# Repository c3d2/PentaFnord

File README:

PentaFnord README
Project Homepage: https://www.c3d2.de/wiki/index.php?title=PentaFnord

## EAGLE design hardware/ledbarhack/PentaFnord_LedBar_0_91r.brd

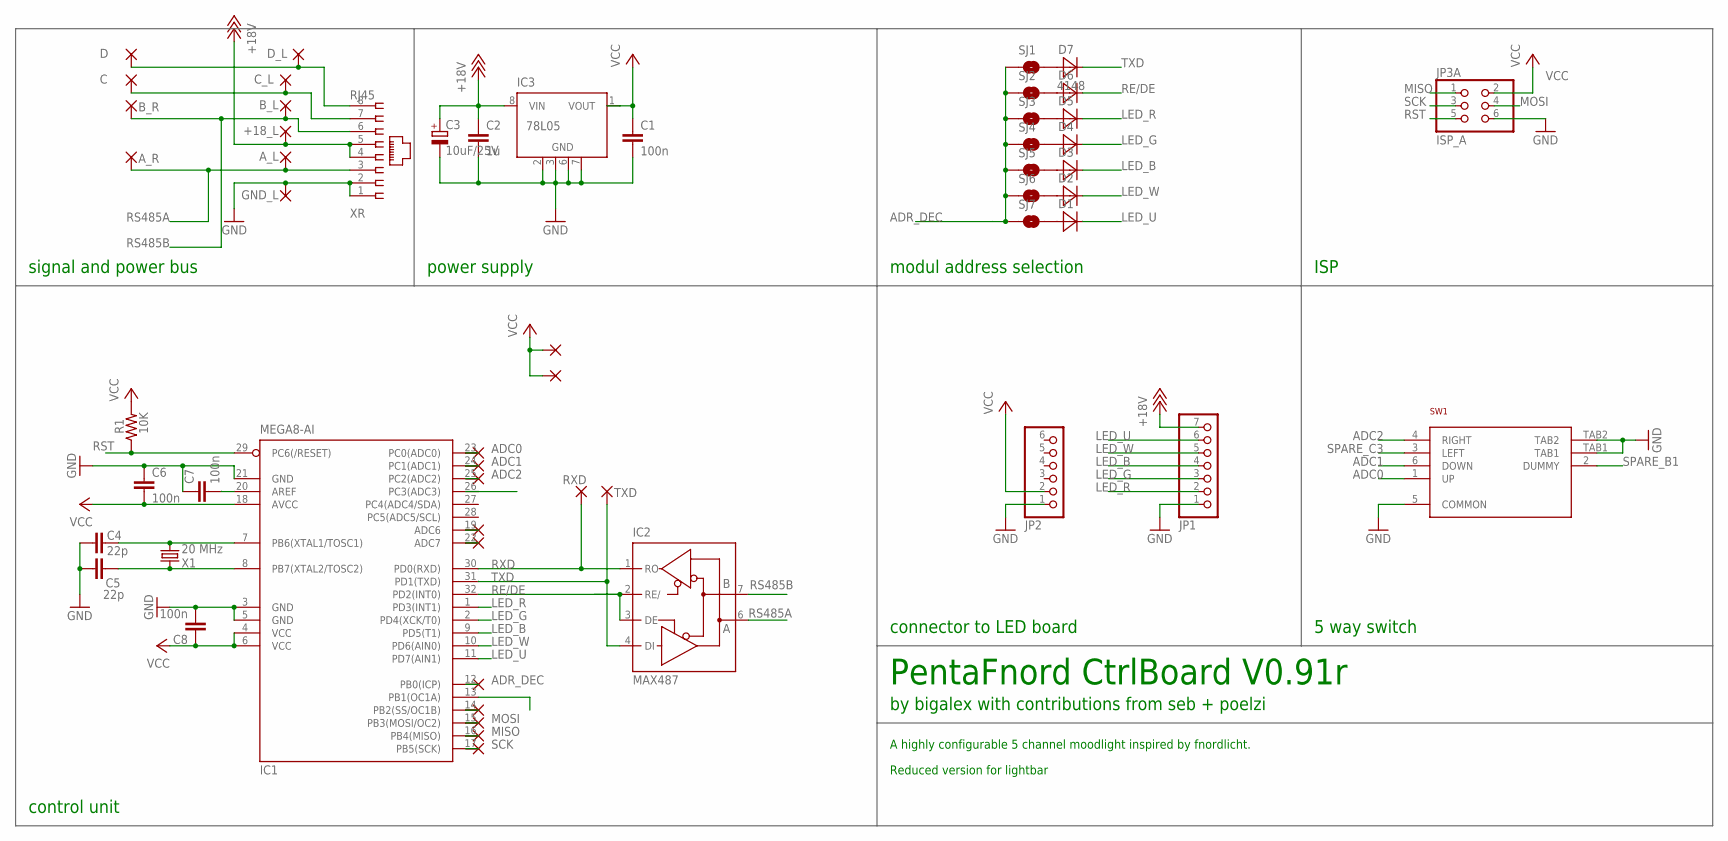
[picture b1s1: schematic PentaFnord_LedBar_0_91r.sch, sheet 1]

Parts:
+18_L: WIREPADSMD2,54-5,08; SMD2,54-5,08
ADC6, ADC7: WIREPADSMD1,27-254; SMD1,27-2,54
A_L: WIREPADSMD2,54-5,08; SMD2,54-5,08
A_R: WIREPADSMD1,27-254; SMD1,27-2,54
B_L: WIREPADSMD2,54-5,08; SMD2,54-5,08
B_R: WIREPADSMD1,27-254; SMD1,27-2,54
C: WIREPADSMD1,27-254; SMD1,27-2,54
C1, C6, C7, C8: 100n; 0805
C2: 1u; 0805
C3: 10uF/25V; SMC_D
C4, C5: 22p; 0805
C_L: WIREPADSMD2,54-5,08; SMD2,54-5,08
D: WIREPADSMD1,27-254; SMD1,27-2,54
D1, D2, D3, D4, D5, D6: DIODE_0805
D7: 4148; DIODE_0805
D_L: WIREPADSMD2,54-5,08; SMD2,54-5,08
GND_L: WIREPADSMD2,54-5,08; SMD2,54-5,08
IC1: MEGA8-AI; TQFP32-08
IC2: MAX487; SO08
IC3: 78L05; SO08
JP1: PINHD-1X07_2.54-SMD-REVERSE; 1X07SMD-REVERSE
JP2: PINHD-1X06_2.54-SMD; 1X06SMD
JP3A: ISP_A; 2X03SMD
PAD3, PAD4: WIREPADSMD1,27-254; SMD1,27-2,54
PB0, PB2, PB3, PB4, PB5: WIREPADSMD1,27-254; SMD1,27-2,54
PC0, PC1, PC2: WIREPADSMD1,27-254; SMD1,27-2,54
R1: 10K; 0805
RXD: WIREPADSMD2,54-5,08; SMD2,54-5,08
SJ1, SJ2, SJ3, SJ4, SJ5, SJ6, SJ7: SOLDERJUMPERNO; SJ_2S-NO
SW1: MCMT5-F-VADAPTED_FOOTPRINT; MCMT5-F-V_ADAPTED
TXD: WIREPADSMD2,54-5,08; SMD2,54-5,08
X1: 20 MHz; HC49UP-SMALL
XR: RJ45; 85502-5008-SMALL

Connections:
+18V: +18_L.1, C2.1, C3.+, IC3.8 (VIN), JP1.7, XR.4, XR.5
ADC0: IC1.23 (PC0(ADC0)), PC0.1, SW1.1 (UP)
ADC1: IC1.24 (PC1(ADC1)), PC1.1, SW1.6 (DOWN)
ADC2: IC1.25 (PC2(ADC2)), PC2.1, SW1.4 (RIGHT)
ADR_DEC: IC1.12 (PB0(ICP)), PB0.1, SJ1.1, SJ2.1, SJ3.1, SJ4.1, SJ5.1, SJ6.1, SJ7.1
GND: C1.2, C2.2, C3.-, C4.1, C5.1, C6.1, C7.1, C8.2, GND_L.1, IC1.3 (GND), IC1.5 (GND), IC1.21 (GND), IC2.5 (GND), IC3.2 (GND), IC3.3 (GND), IC3.6 (GND), IC3.7 (GND), JP1.1, JP2.1, JP3A.6, SW1.5 (COMMON), SW1.TAB1, SW1.TAB2, XR.1, XR.2
LED_B: D3.1 (C), IC1.9 (PD5(T1)), JP1.4
LED_G: D4.1 (C), IC1.2 (PD4(XCK/T0)), JP1.3
LED_R: D5.1 (C), IC1.1 (PD3(INT1)), JP1.2
LED_U: D1.1 (C), IC1.11 (PD7(AIN1)), JP1.6
LED_W: D2.1 (C), IC1.10 (PD6(AIN0)), JP1.5
MISO: IC1.16 (PB4(MISO)), JP3A.1, PB4.1
MOSI: IC1.15 (PB3(MOSI/OC2)), JP3A.4, PB3.1
unnamed: C.1, C_L.1, XR.7
unnamed: D.1, D_L.1, XR.8
unnamed: ADC6.1, IC1.19 (ADC6)
unnamed: ADC7.1, IC1.22 (ADC7)
unnamed: C5.2, IC1.8 (PB7(XTAL2/TOSC2)), X1.2
unnamed: C4.2, IC1.7 (PB6(XTAL1/TOSC1)), X1.1
unnamed: C7.2, IC1.20 (AREF)
unnamed: D7.2 (A), SJ1.2
unnamed: D6.2 (A), SJ2.2
unnamed: D5.2 (A), SJ3.2
unnamed: D4.2 (A), SJ4.2
unnamed: D3.2 (A), SJ5.2
unnamed: D2.2 (A), SJ6.2
unnamed: D1.2 (A), SJ7.2
unnamed: IC1.14 (PB2(SS/OC1B)), PB2.1
RE/DE: D6.1 (C), IC1.32 (PD2(INT0)), IC2.2 (RE/), IC2.3 (DE)
RS485A: A_L.1, A_R.1, IC2.6 (A), XR.3
RS485B: B_L.1, B_R.1, IC2.7 (B), XR.6
RST: IC1.29 (PC6(/RESET)), JP3A.5, R1.1
RXD: IC1.30 (PD0(RXD)), IC2.1 (RO), RXD.1
SCK: IC1.17 (PB5(SCK)), JP3A.3, PB5.1
SPARE_B1: IC1.13 (PB1(OC1A)), SW1.2 (DUMMY)
SPARE_C3: IC1.26 (PC3(ADC3)), SW1.3 (LEFT)
TXD: D7.1 (C), IC1.31 (PD1(TXD)), IC2.4 (DI), TXD.1
VCC: C1.1, C6.2, C8.1, IC1.4 (VCC), IC1.6 (VCC), IC1.18 (AVCC), IC2.8 (VCC), IC3.1 (VOUT), JP2.2, JP3A.2, PAD3.1, PAD4.1, R1.2

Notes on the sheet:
signal and power bus
power supply
control unit
PentaFnord CtrlBoard V0.91r
by bigalex with contributions from seb + poelzi
A highly configurable 5 channel moodlight inspired by fnordlicht.
modul address selection
ISP
connector to LED board
5 way switch
Reduced version for lightbar

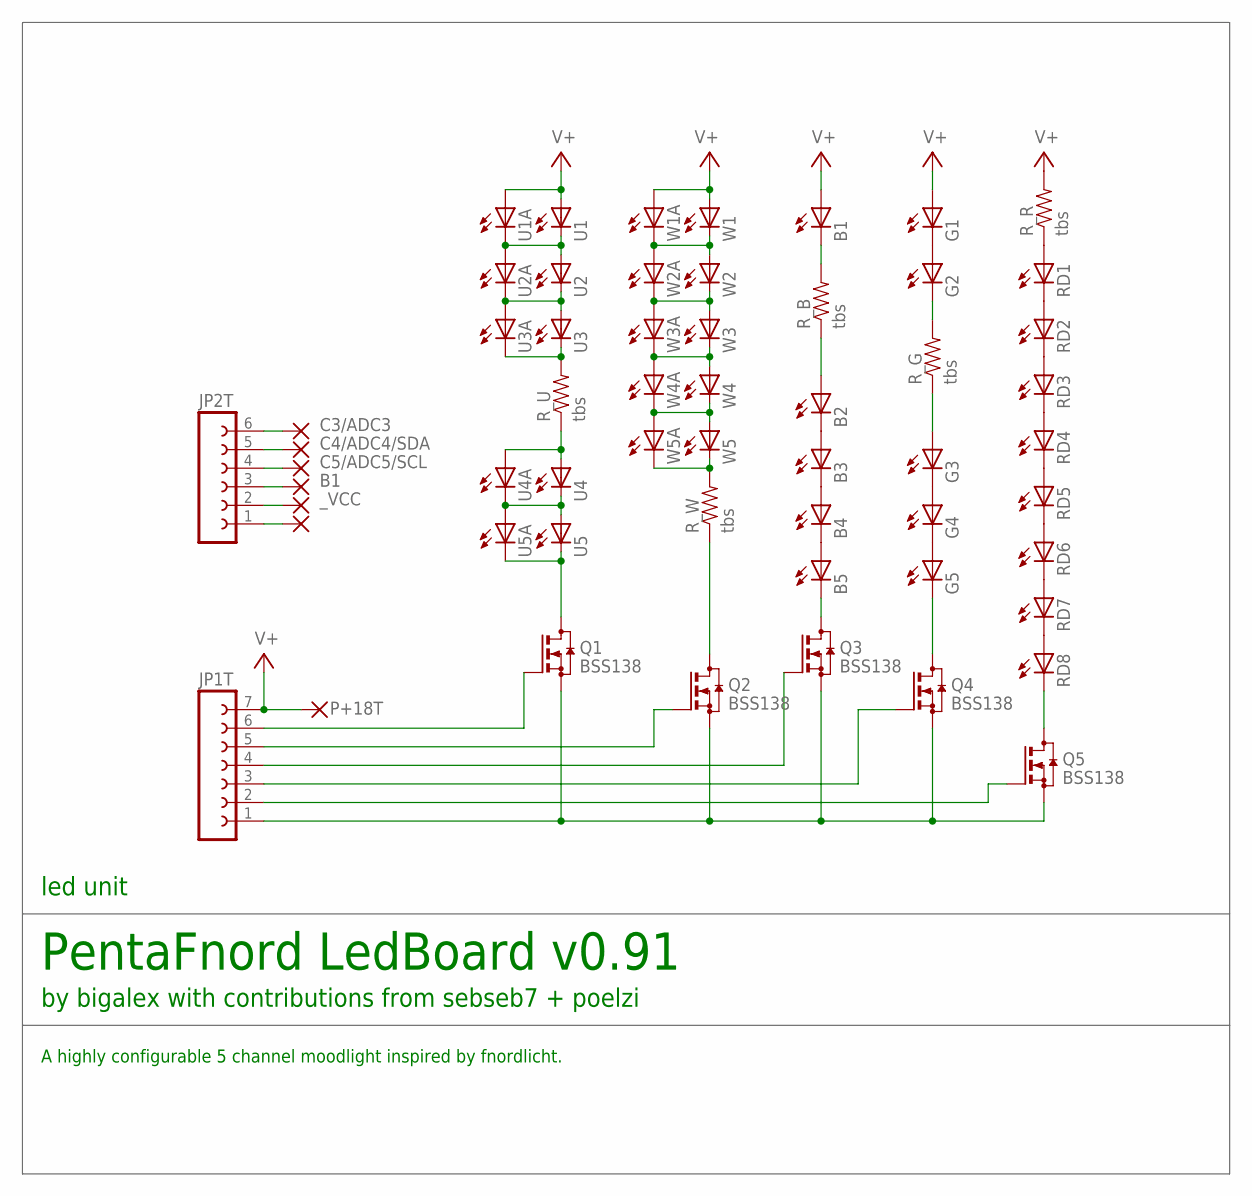
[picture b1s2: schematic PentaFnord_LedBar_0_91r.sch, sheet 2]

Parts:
B1, B2, B3, B4, B5: LED5MM
G1, G2, G3, G4, G5: LED5MM
JP1T: FE07-1; FE07
JP2T: FE06-1; FE06
P+5T, P+18T: WIREPAD2,54/0,8; 2,54/0,8
PB1T: WIREPAD2,54/0,8; 2,54/0,8
PC3T, PC4T, PC5T: WIREPAD2,54/0,8; 2,54/0,8
PGNDT1: WIREPAD2,54/0,8; 2,54/0,8
Q1, Q2, Q3, Q4, Q5: BSS138; SOT23
RD1, RD2, RD3, RD4, RD5, RD6, RD7, RD8: LED5MM
R_B: tbs; 1206
R_G: tbs; 1206
R_R: tbs; 1206
R_U: tbs; 1206
R_W: tbs; 1206
U1, U2, U3, U4, U5: NICHIA_NSSL157T-H3; PLCC2
U1A, U2A, U3A, U4A, U5A: LED5MM
W1, W2, W3, W4, W5: NICHIA_NSSL157T-H3
W1A, W2A, W3A, W4A, W5A: LED5MM

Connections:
B1: JP2T.3, PB1T.1
C3/ADC3: JP2T.6, PC3T.1
C4/ADC4/SDA: JP2T.5, PC4T.1
C5/ADC5/SCL: JP2T.4, PC5T.1
GND_T: JP1T.1, JP2T.1, PGNDT1.1, Q1.2 (S), Q2.2 (S), Q3.2 (S), Q4.2 (S), Q5.2 (S)
unnamed: U1.P$1 (C), U1A.K (C), U2.P$2 (A), U2A.A
unnamed: W4.K@1 (C), W4A.K (C), W5.A@2 (A), W5A.A
unnamed: Q1.3 (D), U5.P$1 (C), U5A.K (C)
unnamed: Q2.3 (D), R_W.1
unnamed: W3.K@1 (C), W3A.K (C), W4.A@2 (A), W4A.A
unnamed: R_U.2, U3.P$1 (C), U3A.K (C)
unnamed: U2.P$1 (C), U2A.K (C), U3.P$2 (A), U3A.A
unnamed: U4.P$1 (C), U4A.K (C), U5.P$2 (A), U5A.A
unnamed: G1.K (C), G2.A
unnamed: B5.K (C), Q3.3 (D)
unnamed: G3.K (C), G4.A
unnamed: G4.K (C), G5.A
unnamed: B2.K (C), B3.A
unnamed: B3.K (C), B4.A
unnamed: B4.K (C), B5.A
unnamed: G5.K (C), Q4.3 (D)
unnamed: RD1.K (C), RD2.A
unnamed: RD2.K (C), RD3.A
unnamed: RD3.K (C), RD4.A
unnamed: RD4.K (C), RD5.A
unnamed: RD5.K (C), RD6.A
unnamed: RD6.K (C), RD7.A
unnamed: RD1.A, R_R.1
unnamed: RD7.K (C), RD8.A
unnamed: B1.K (C), R_B.2
unnamed: Q5.3 (D), RD8.K (C)
unnamed: B2.A, R_B.1
unnamed: G2.K (C), R_G.2
unnamed: G3.A, R_G.1
unnamed: W2.K@1 (C), W2A.K (C), W3.A@2 (A), W3A.A
unnamed: R_U.1, U4.P$2 (A), U4A.A
unnamed: R_W.2, W5.K@1 (C), W5A.K (C)
unnamed: JP1T.6, Q1.1 (G)
unnamed: JP1T.5, Q2.1 (G)
unnamed: JP1T.3, Q4.1 (G)
unnamed: JP1T.4, Q3.1 (G)
unnamed: JP1T.2, Q5.1 (G)
unnamed: W1.K@1 (C), W1A.K (C), W2.A@2 (A), W2A.A
V+: B1.A, G1.A, JP1T.7, P+18T.1, R_R.2, U1.P$2 (A), U1A.A, W1.A@2 (A), W1A.A
_VCC: JP2T.2, P+5T.1

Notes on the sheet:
led unit
PentaFnord LedBoard v0.91
by bigalex with contributions from sebseb7 + poelzi
A highly configurable 5 channel moodlight inspired by fnordlicht.

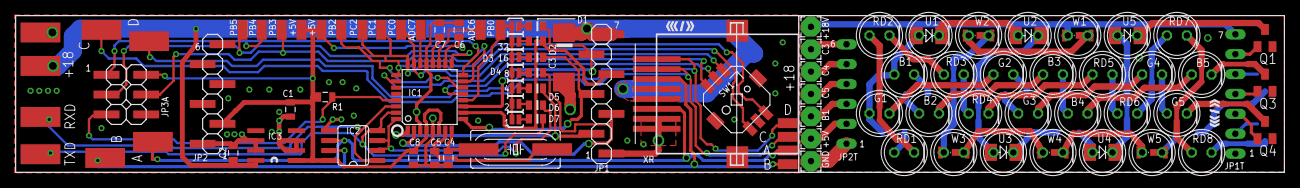
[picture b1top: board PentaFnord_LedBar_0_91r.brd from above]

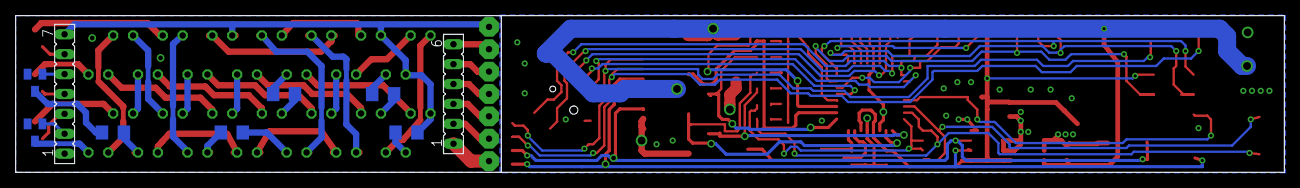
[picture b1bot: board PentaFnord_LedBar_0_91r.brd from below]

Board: 2 copper layers, 162.0 x 20.0 mm, 113 parts (9 on the bottom side), 83 nets.

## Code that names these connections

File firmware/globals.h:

/*
 * PentaFnord Firmware
 *
 * by Alexander Lorz <bigalex@gmx.de>
 *
 *
 * Parts of this software are derived work, originating from the fine
 * fnordlicht firmware (see http://lochraster.org/fnordlichtmini)
 * by Alexander Neumann <alexander@bumpern.de> and Lars Noschinski
 * <lars@public.noschinski.de>, originally published and of course
 * republished under the terms of the GNU General Public License version 3
 *
 * This program is free software: you can redistribute it and/or modify it
 * under the terms of the GNU General Public License version 3 as published by
 * the Free Software Foundation.
 *
 * This program is distributed in the hope that it will be useful, but WITHOUT
 * ANY WARRANTY; without even the implied warranty of MERCHANTABILITY or
 * FITNESS FOR A PARTICULAR PURPOSE.  See the GNU General Public License for
 * more details.
 *
 * You should have received a copy of the GNU General Public License along with
 * this program.  If not, see <http://www.gnu.org/licenses/>.
 */

#ifndef GLOBALS_H
#define GLOBALS_H

//#include <stdbool.h>
#include <avr/version.h>
#include "lib/common.h"


/* check for avr-libc version */
#if __AVR_LIBC_VERSION__ < 10600UL
#error "newer libc version (>= 1.6.0) needed!"
#endif

/* check if cpu speed is defined */
#ifndef F_CPU
#error "please define F_CPU! (see Makefile)"
#endif

/* check if this cpu is supported */
#if !(defined(__AVR_ATmega48__) || defined(__AVR_ATmega168__))
#error "this cpu is not supported yet!"
#endif

/* Port D is used for PWM with:
 * 		PD3: red
 * 		PD4: green
 * 		PD5: blue
 * 		PD6: white
 * 		PD7: ultra violet
 */

#define PWM_PORT D
#define PWM_CHANNELS 5
#define PWM_SHIFT 3
#define PWM_CHANNEL_MASK (_BV(PD3) | _BV(PD4) | _BV(PD5) | _BV(PD6)| _BV(PD7))	//This is Red Green Blue White UV

/* min brightness level */
#define PWM_MIN_BRIGHTNESS 0

#ifndef EXTERN
#define EXTERN extern
#endif


EXTERN uint8_t G_hwaddr;
EXTERN uint8_t G_swaddr;



#endif				/* GLOBALS_H */

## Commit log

2011-09-24 initial version of README
2011-09-25 Initial Version of schematics and board layout
2011-10-03 Not entirely incomplete version of schematics. LED placement on PCB allowing for 25mm x 25 mm profile (assembled PCB width < 21 mm)
2011-10-04 Routed I2C to upper board. Pullup resistors for I2C added.
2011-10-05 Board interconector placement, RJ45 SMD footprint added, modul address decoding added, lots of other improvements
2011-10-06 Upper board routed
2011-10-07 Started Layout of bottom PCB
2011-10-07 some routing done, but more left
2011-10-08 Some routing improvements, replaced 1805 by smaller 78L05
2011-10-09 Some more routing done
2011-10-10 Even much more routing done
2011-10-11 routing
2011-10-11 some ripup due to insufficient groundpath in groundplane
2011-10-12 some routing
2011-10-13 routin
2011-10-19 routing, placement print, bigger blocking Cs, value for basis resistor adapted
2011-10-19 labeling
2011-10-20 groundplanes, placement print placing, some renaming of components
2011-10-21 parts enumeration, placement print
2011-10-21 nearing completion. all labels for names and placement ... ummm ... placed
2011-10-22 Teileliste erstellt
2011-10-22 Renaming for save experimenting with 5-way-switch instead of 3 tactile buttons
2011-10-22 Initial checkin. Trying to integrate a 5-way-switch.
2011-10-23 Some schematics beautification. 5 way switch fully integrated
2011-10-23 Replacded 1206 resistors for RGBU-Leds with 805 to avoid keepout problems. Version imprint on boards updated.
2011-10-23 partslist updated
2011-10-23 Pinout-Doku added
2011-10-28 version 3 created for integrating feedback
2011-11-01 Integrating recoomendations and improvements
2011-11-17 Added optional terminator an bias resistors for RS485 (with solder jumpers)
2011-11-21 polishing routing
2011-11-24 moar features, will hack correct pinhead distance for pads (or at least try to)
2011-12-05 realigned solderpads for general signal breakouts to support optional mounting of pinheader
2011-12-11 v0.4 layout, print
2011-12-18 c3d2-logo CI conform
2012-01-01 some things done (hell yeah, i know this is a bit unspecific, but who cares)
2012-01-07 Trying to integrate two more freakin line protection resistors into this overcrowded board
2012-01-09 smaller resistors and solderjumpers, some ripup to make room for lager (and mich, much cheaper) crytstal
2012-01-10 crash recovery
2012-01-10 crash recovered, routing done, placement print donde, lets look forward what we might find to improve
2012-01-10 conflict resolved
2012-01-12 replaced diodes with 0805 type, rank for groundplane fixes unnecessary trestrict
2012-01-16 added .gitignore
2012-01-16 editor backup files into .gitignore
2012-01-19 Added tatnatl SMC-D capacitor but found no place for it yet
2012-01-19 smaller footprint for rj45 connector avoids violation of board boundaries
2012-01-19 electrolytic cap placed after some rearangements, still need to tidy up
2012-01-20 already quite nice, did a bit of tidying up
2012-01-20 repo maintenance
2012-01-22 last edit (GND via) before splitting up files for Led- and Ctrl-Board
2012-01-22 design files splitted into LedBoard and CtrlBoard, tidied up a bit
2012-01-23 footprint of 5way switch optimized, some distance optimizations for components
2012-01-25 added library with slightly modified components
2012-01-25 Polarity markings for electrolytic c in t_place
2012-01-27 pimped the readme
2012-01-28 minor additions to README
2012-02-03 sync
2012-02-05 trying to route additional bus wires fromone end of the board to the other. insane, but will work, not yet done.
2012-02-05 alle data bus wires connected troughout the board
2012-02-08 genesis constant current led board
2012-02-10 first completetely routed draft of power led board
2012-02-10 renamed power led board
2012-02-11 started arranging placement print
2012-02-12 Placement print finished so far
2012-02-13 proposal for routing under inductivities
2012-02-14 replaced smd inductivities with wired components
2012-02-16 routing for wired inductivities done
2012-02-27 Added some items to readme
2012-04-25 specified values for C3 and D1
2012-04-26 added image of board001
2012-04-26 embedded image in readme.mkd
2012-04-26 markdown fix (embedded image in readme.mkd)
2012-04-29 Documented First Time Operation and (mostly avoidable) bugs encountered when assembling the board and powering it up for the first time
2012-05-01 added meassured values vor the sum of forward voltages in each led strand
2012-05-01 linebreaks in tabe for forward voltages in each led strand
2012-05-01 one more linebreak in table for forward voltages in each led strand
2012-05-02 values for resistors (and measured current) in place added
2012-05-28 firmware genesis
2012-05-29 alternative exponential pwm table
2012-05-29 starting to experiment with isr
2012-05-31 optimized ISR
2012-06-03 removed functions and structures for specifying and converting colors as HSV values to keep code lean and avoid using to much memory for barely used functions
2012-06-05 now all buttons are read
2012-06-05 fixed bug in fadinng
2012-06-10 starting rework for LED Board
2012-06-10 renaming CtrlBoard for integrating future fixes
2012-06-10 PentaFnord_CtrlBoard_0_91.b#1
    corrected wrong numbering of JP2 pins, version ID on bottom went up from 0.9 to 0.91
2012-06-10 recvery point. starting to integrate rs485 routines
2012-06-10 uart protocols and first test added
2012-06-17 added firmware Makefile for easy build from vim
2012-06-17 some refactoring
2012-06-17 fusebits im Makefile entsprechend Alex’ Vorgabe
2012-06-17 Fixed state machine, so button states do no longer hang in states that are not asked for (and therefore will not be reset)
2012-06-17 using <util/setbaud.h> for USART baudrate definition
2012-06-17 some fixes
2012-06-17 fixed warning implicit function
2012-06-18 fixed many warnings, colorpalette added
2012-06-25 replaced values of R6-R9 with value in use (5K instead of 5.6K)
2012-06-25 fiddling with the RS485 communication
2012-06-25 some routing for improved LED Board done
2012-07-26 genesis for remote control firmware using USART/RS485
2012-10-23 values for smd led board
2012-10-28 Deleted Project Status, shortened README
2012-10-28 added manufactured version of 0.91 LED board
2012-10-28 added placement view of PFCB 0.91
2012-10-28 added image of PFCB
2012-10-28 Numbering of ICs correchted
2012-10-28 parts and prices for PFCB added
2012-10-28 added placement schematics for PFLB
2012-10-28 added schematics for PFLB
2012-10-28 parts list and pricing for LED board
2012-11-10 LedBar - reduced board.
2012-11-10 moar routing
2012-11-10 routing done
2012-12-12 archived manufactured Version foLedBar
2013-01-19 file format change to new eagle 6 (xml instead of binary)
2013-01-20 usart communication works now (at least receiving with 115200)
2013-01-20 repo cleanup and sync with working copy
2013-01-20 linked to led bar hack
2013-01-20 simplified Makefile with faster programming
2013-01-20 beutified button detection
2013-01-26 xternalized functions for reading comands from RS485 bus
2013-01-26 fixed uC type from m88 to m48
2013-01-26 removed deprecated stuff, added vars for global HW and SW address
2013-01-26 hardware address decoding
2013-01-26 Baudrate to 500.000, some convenince functions
2013-01-26 directly setting RGBWU values without fading
2013-01-26 some optimized memcopying
2013-01-26 i can haz lightknot protocoll (at least a bit)
